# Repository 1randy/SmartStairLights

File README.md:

# Smart Stair Lights

A ESP / Arduino based Automatic Stair Liights with WS2801 LED Driver Board.

:warning: **Use at your own risk, always check your layout before manufacturing!**

## Features

 - support for Infrared, PIR, Mechanical Sensors
 - cascadable WS2801 Board
 - Dimmed LEDs when inactive

## Planned Features

 - MQTT Support for remote activating

## Schematic

<br>
[PDF download](https://raw.githubusercontent.com/1randy/SmartStairLights/master/hardware/docu/WS2801_ledmodule_rev2.sch.pdf)

## Board

**Top side**

You can order the PCB of this board at [elecrow][1] with the supplied gerbers.

## Links

[1]: https://www.elecrow.com/pcb-manufacturing.html

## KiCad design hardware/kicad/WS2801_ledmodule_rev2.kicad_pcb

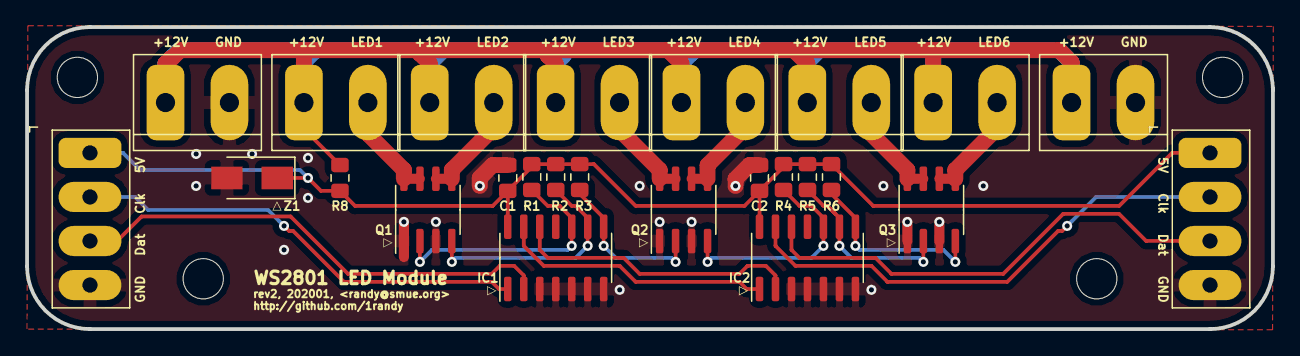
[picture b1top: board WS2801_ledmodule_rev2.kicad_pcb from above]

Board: 2 copper layers, 99.0 x 24.0 mm, 28 parts (0 on the bottom side), 21 nets.

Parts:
5V   Clk   Dat   GND: Conn_01x04_Male; TerminalBlock_Phoenix_PT-1,5-4-3.5-H_1x04_P3.50mm_Horizontal
+12V    GND, +12V    GND#2, +12V    LED1, +12V    LED2, +12V    LED3, +12V    LED4, +12V    LED5, +12V    LED6: Conn_01x02_Male; TerminalBlock_bornier-2_P5.08mm
C1, C2: 100n; C_0805_2012Metric_Pad1.15x1.40mm_HandSolder
GND   Dat   Clk   5V: Conn_01x04_Male; TerminalBlock_Phoenix_PT-1,5-4-3.5-H_1x04_P3.50mm_Horizontal
H2, H3, H4: MountingHole; MountingHole_3.2mm_M3
IC1, IC2: WS2801; SOIC-14_3.9x8.7mm_P1.27mm
Q1, Q2, Q3: IRF7301PBF; SOIC-8_3.9x4.9mm_P1.27mm
R1, R2, R3, R4, R5, R6: 10k; R_0805_2012Metric_Pad1.15x1.40mm_HandSolder
R8: 2k2; R_0805_2012Metric_Pad1.15x1.40mm_HandSolder
Z1: 5v1; D_SMA

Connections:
+12V: +12V GND.1, +12V GND#2.1, +12V LED1.1, +12V LED2.1, +12V LED3.1, +12V LED4.1, +12V LED5.1, +12V LED6.1, R8.2
/Clock_In: GND Dat Clk 5V.2, IC1.1
/Clock_Out: 5V Clk Dat GND.2, IC2.13
/Data_In: GND Dat Clk 5V.3, IC1.2
/Data_Out: 5V Clk Dat GND.3, IC2.12
/LED1: IC1.10, Q1.2, R1.1
/LED2: IC1.9, Q1.4, R2.1
/LED3: IC1.8, Q2.2, R3.1
/LED4: IC2.10, Q2.4, R4.1
/LED5: IC2.9, Q3.2, R5.1
/LED6: IC2.8, Q3.4, R6.1
/Vcc: 5V Clk Dat GND.1, C1.1, C2.1, GND Dat Clk 5V.1, IC1.14, IC2.14, R1.2, R2.2, R3.2, R4.2, R5.2, R6.2, R8.1, Z1.1
GND: 5V Clk Dat GND.4, +12V GND.2, +12V GND#2.2, C1.2, C2.2, GND Dat Clk 5V.4, IC1.3, IC1.4, IC1.5, IC1.6, IC1.7, IC2.3, IC2.4, IC2.5, IC2.6, IC2.7, Q1.1, Q1.3, Q2.1, Q2.3, Q3.1, Q3.3, Z1.2
unnamed: IC1.12, IC2.2
unnamed: IC1.13, IC2.1
unnamed: +12V LED1.2, Q1.7, Q1.8
unnamed: +12V LED2.2, Q1.5, Q1.6
unnamed: +12V LED3.2, Q2.7, Q2.8
unnamed: +12V LED4.2, Q2.5, Q2.6
unnamed: +12V LED5.2, Q3.7, Q3.8
unnamed: +12V LED6.2, Q3.5, Q3.6

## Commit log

2020-03-27 update gitignore
2020-03-27 initial upload
2020-03-27 add README
2020-04-20 make pullups switchable (PIR sensor support)
